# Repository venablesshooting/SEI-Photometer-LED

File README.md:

# SEI-Photometer-LED
A public repository for storing the files related to the LED conversion of the SEI Photometer based off of Huw Finney's work

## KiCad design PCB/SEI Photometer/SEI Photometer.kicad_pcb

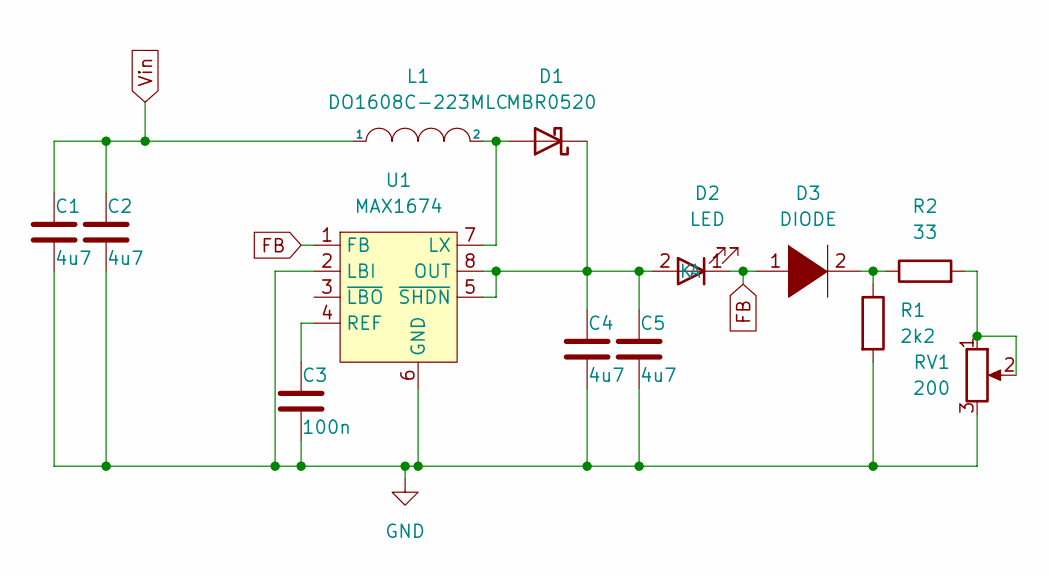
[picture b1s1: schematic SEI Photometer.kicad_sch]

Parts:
C1, C2, C4, C5: 4u7; C_0603_1608Metric
C3: 100n; C_0603_1608Metric
D1: MBR0520; D_SOD-123
D2: LED; LEDRD254W50D405H508
D3: DIODE; D_MELF
L1: DO1608C-223MLC; DO1608C
R1: 2k2; R_0603_1608Metric
R2: 33; R_0603_1608Metric
RV1: 200; PANASONIC_EVM3YSX50B52
U1: MAX1674; SOP50P490X110-8N

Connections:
FB: D2.1 (K), D3.1 (K), U1.1 (FB)
GND: C1.2, C2.2, C3.2, C4.2, C5.2, R1.2, RV1.3, U1.2 (LBI), U1.6 (GND); also elsewhere on the board
unnamed: D1.2 (A), L1.2, U1.7 (LX)
unnamed: C4.1, C5.1, D1.1 (K), D2.2 (A), U1.5 (~SHDN), U1.8 (OUT)
unnamed: D3.2 (A), R1.1, R2.1
unnamed: R2.2, RV1.1, RV1.2
unnamed 6: C3.1, U1.4 (REF); also elsewhere on the board
Vin: C1.1, C2.1, L1.1

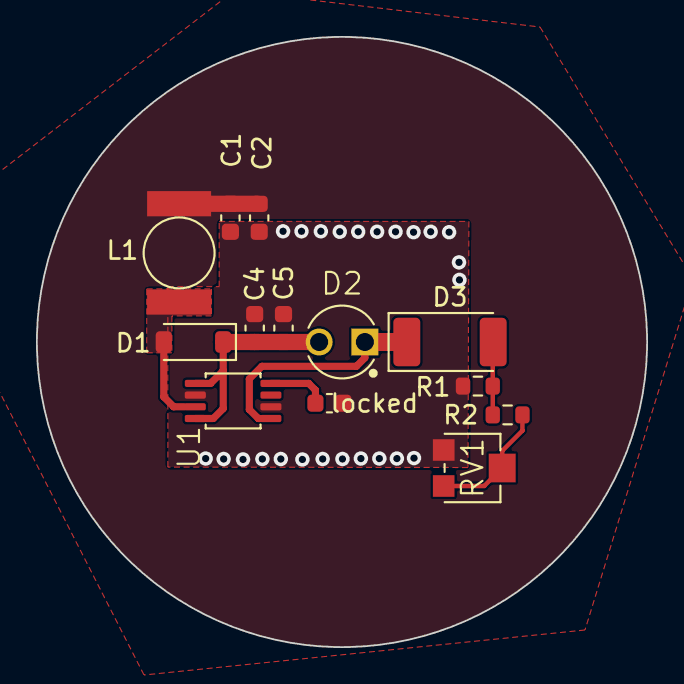
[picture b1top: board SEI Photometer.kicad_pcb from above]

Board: 2 copper layers, 33.9 x 33.9 mm, 13 parts (0 on the bottom side), 8 nets.

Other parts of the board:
locked: 100n; C_0603_1608Metric

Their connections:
GND: locked.2; also elsewhere on the board
unnamed 6: locked.1; also elsewhere on the board

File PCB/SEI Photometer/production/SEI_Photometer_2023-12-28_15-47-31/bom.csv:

Designator,Footprint,Quantity,Value,LCSC Part #
"C1, C2, C4, C5",0603,4,4u7,
C3,0603,1,100n,
D1,D_SOD-123,1,MBR0520,
D2,LEDRD254W50D405H508,1,LED,
D3,D_MELF,1,DIODE,
L1,DO1608C,1,22u,
R1,0603,1,2k2,
R2,0603,1,33,
RV1,PANASONIC_EVM3YSX50B52,1,200,
U1,SOP50P490X110-8N,1,MAX1674,

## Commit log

2023-12-28 changed the positive and negative terminals
